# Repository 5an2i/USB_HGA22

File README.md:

# USB_HGA22
HGA22 RF signal receiver with STM32C071 Cortex-M0+ MCU with USB interface

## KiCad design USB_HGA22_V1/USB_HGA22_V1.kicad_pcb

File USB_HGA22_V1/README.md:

# Project Summary - USB_HGA22_V1

## English Description

### Overview
USB_HGA22_V1 is a hardware and software project designed to receive and process signals from the **HGA22** transmitter located in Lakihegy, Hungary. The HGA22 station operates at 135.6 kHz using FSK modulation as part of the EFR Teleswitch system. Unlike standard DCF77 receivers, HGA22 provides much faster time synchronization (every 10 seconds). This project interfaces the receiver with a computer via USB using a modern STM32C071 microcontroller.

### Technical Details
- Microcontroller: **STM32C071** (Arm Cortex-M0+, featuring crystal-less USB support).
- Signal Source: HGA22 (135.6 kHz, FSK modulation, 200 bps).
- Functionality: Decoding the EFR/Teleswitch protocol for precise time acquisition and power management command monitoring.
- Connection: USB 2.0 Full Speed (CDC or HID class) for direct PC integration.

### Key Features
- High-speed synchronization compared to traditional longwave time signals.
- Utilization of the internal 48 MHz RC oscillator (CRS) of the STM32C071 for crystal-less USB communication.
- Low-power design suitable for continuous background operation.

---

## Magyar nyelvű összefoglaló

### Áttekintés
Az USB_HGA22_V1 egy hardveres és szoftveres projekt, amelyet a lakihegyi **HGA22** adó jeleinek vételére és feldolgozására terveztek. A HGA22 állomás 135,6 kHz-es frekvencián, FSK modulációval sugároz az európai EFR Teleswitch rendszer részeként. A DCF77-tel ellentétben a HGA22 sokkal gyakoribb (10 másodpercenkénti) időszinkronizációt tesz lehetővé. A projekt egy modern STM32C071 mikrokontroller segítségével illeszti a vevőegységet a számítógéphez USB-n keresztül.

### Technikai részletek
- Mikrokontroller: **STM32C071** (Arm Cortex-M0+, integrált USB támogatással).
- Jelforrás: HGA22 (135,6 kHz, FSK moduláció, 200 bps adatsebesség).
- Funkció: Az EFR/Teleswitch protokoll dekódolása pontos időnyeréshez vagy vezérlési parancsok (pl. tarifaváltás) monitorozásához.
- Kapcsolat: USB 2.0 Full Speed interfész a közvetlen PC-s kapcsolathoz.

### Főbb jellemzők
- A hagyományos hosszúhullámú időjelekhez képest lényegesen gyorsabb szinkronizáció.
- Az STM32C071 belső 48 MHz-es oszcillátorának (CRS) használata, így nincs szükség külső kvarckristályra az USB kommunikációhoz.
- Alacsony fogyasztású kialakítás, amely ideális folyamatos háttérüzemre.

## Schematic

### Revision 1.0

## Visuals

### Top View

### Bottom View

### Panelized Board

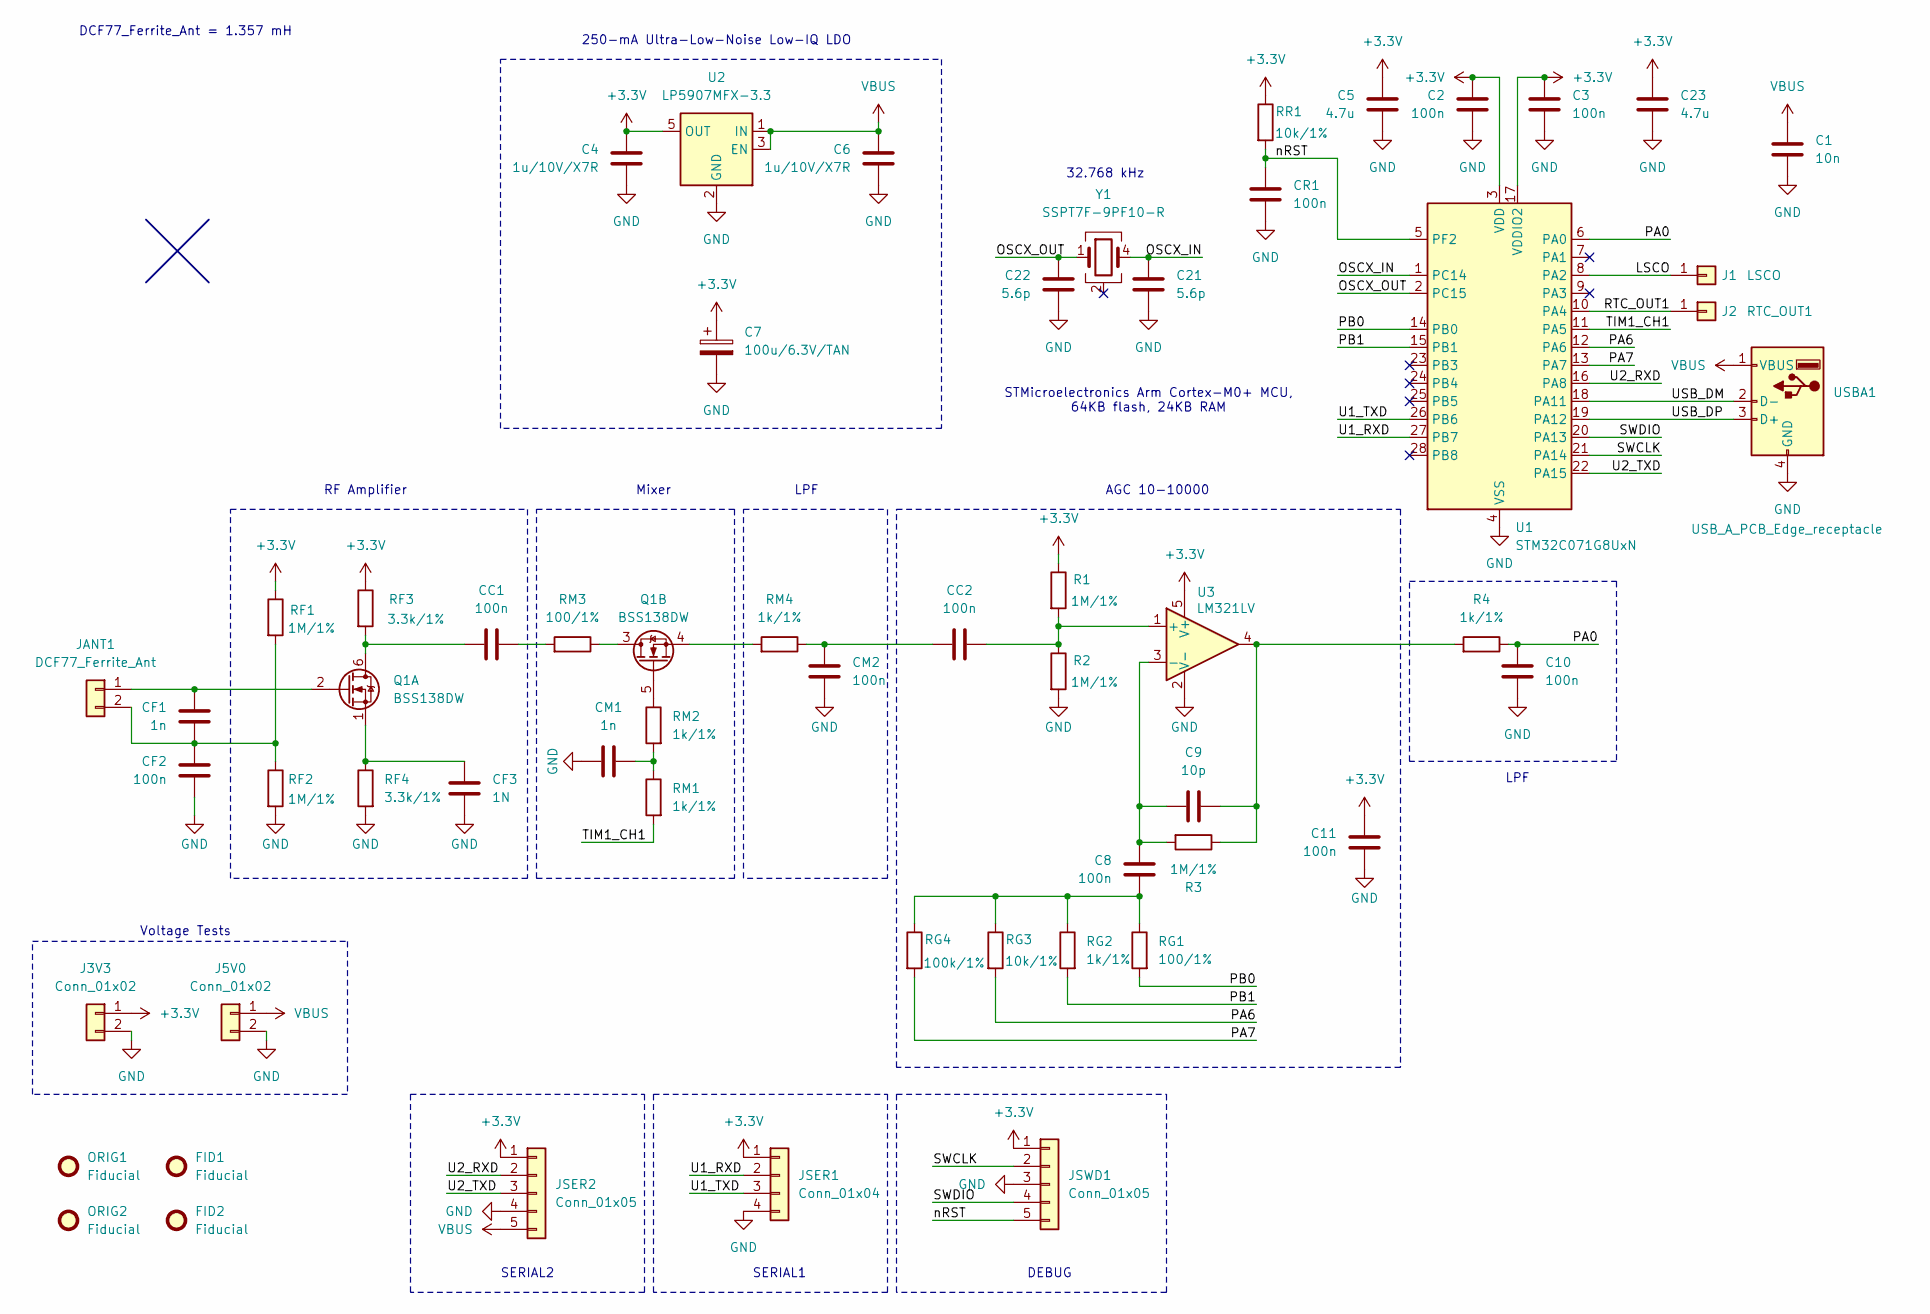
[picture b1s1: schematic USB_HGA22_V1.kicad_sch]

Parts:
C1: 10n; C_0402_1005Metric_Pad0.74x0.62mm_HandSolder
C2, C3, C8, C10, C11: 100n; C_0402_1005Metric_Pad0.74x0.62mm_HandSolder
C4, C6: 1u/10V/X7R; C_0603_1608Metric_Pad1.08x0.95mm_HandSolder
C5, C23: 4.7u; C_0603_1608Metric_Pad1.08x0.95mm_HandSolder
C7: 100u/6.3V/TAN; CP_EIA-3528-21_Kemet-B_HandSolder
C9: 10p; C_0402_1005Metric_Pad0.74x0.62mm_HandSolder
C21, C22: 5.6p; C_0402_1005Metric_Pad0.74x0.62mm_HandSolder
CC1, CC2: 100n; C_0402_1005Metric_Pad0.74x0.62mm_HandSolder
CF1: 1n; C_0805_2012Metric_Pad1.18x1.45mm_HandSolder
CF2: 100n; C_0402_1005Metric_Pad0.74x0.62mm_HandSolder
CF3: 1N; C_0402_1005Metric_Pad0.74x0.62mm_HandSolder
CM1: 1n; C_0402_1005Metric_Pad0.74x0.62mm_HandSolder
CM2: 100n; C_0402_1005Metric_Pad0.74x0.62mm_HandSolder
CR1: 100n; C_0402_1005Metric_Pad0.74x0.62mm_HandSolder
FID1, FID2: Fiducial; Fiducial_1.5mm_Mask3mm
J1: LSCO; SolderWirePad_1x01_SMD_1x2mm
J2: RTC_OUT1; SolderWirePad_1x01_SMD_1x2mm
J3V3, J5V0: Conn_01x02; PinHeader_1x02_P2.54mm_Vertical
JANT1: DCF77_Ferrite_Ant; PinHeader_1x02_P2.54mm_Vertical
JSER1: Conn_01x04; PinHeader_1x04_P2.54mm_Vertical
JSER2: Conn_01x05; PinHeader_1x05_P2.54mm_Vertical
JSWD1: Conn_01x05; PinHeader_1x05_P2.54mm_Vertical
ORIG1, ORIG2: Fiducial; Fiducial_Cross_1.5mm_Mask2mm
Q1: BSS138DW; SOT-363_SC-70-6_Handsoldering
R1, R2, R3: 1M/1%; R_0402_1005Metric_Pad0.72x0.64mm_HandSolder
R4: 1k/1%; R_0402_1005Metric_Pad0.72x0.64mm_HandSolder
RF1, RF2: 1M/1%; R_0402_1005Metric_Pad0.72x0.64mm_HandSolder
RF3, RF4: 3.3k/1%; R_0402_1005Metric_Pad0.72x0.64mm_HandSolder
RG1: 100/1%; R_0402_1005Metric_Pad0.72x0.64mm_HandSolder
RG2: 1k/1%; R_0402_1005Metric_Pad0.72x0.64mm_HandSolder
RG3: 10k/1%; R_0402_1005Metric_Pad0.72x0.64mm_HandSolder
RG4: 100k/1%; R_0402_1005Metric_Pad0.72x0.64mm_HandSolder
RM1, RM2, RM4: 1k/1%; R_0402_1005Metric_Pad0.72x0.64mm_HandSolder
RM3: 100/1%; R_0402_1005Metric_Pad0.72x0.64mm_HandSolder
RR1: 10k/1%; R_0402_1005Metric_Pad0.72x0.64mm_HandSolder
U1: STM32C071G8UxN; QFN-28_4x4mm_P0.5mm
U2: LP5907MFX-3.3; SOT-23-5
U3: LM321LV; SOT-23-5
USBA1: USB_A_PCB_Edge_receptacle
Y1: SSPT7F-9PF10-R; Crystal_SMD_Seiko_SSPT7F-4Pin_6.7x1.5mm_HandSoldering

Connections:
+3.3V: C2.1, C3.1, C4.1, C5.1, C7.1, C11.1, C23.1, J3V3.1, JSER1.1, JSER2.1, JSWD1.1, R1.1, RF1.1, RF3.1, RR1.1, U1.3 (VDD), U1.17 (VDDIO2), U2.5 (OUT), U3.5 (V+)
/LSCO: J1.1 (Pin_1_1), U1.8 (PA2)
/OSCX_IN: C21.1, U1.1 (PC14), Y1.4
/OSCX_OUT: C22.1, U1.2 (PC15), Y1.1
/PA0: C10.1, R4.1, U1.6 (PA0)
/PA6: RG3.2, U1.12 (PA6)
/PA7: RG4.2, U1.13 (PA7)
/PB0: RG1.2, U1.14 (PB0)
/PB1: RG2.2, U1.15 (PB1)
/RTC_OUT1: J2.1 (Pin_1_1), U1.10 (PA4)
/SWCLK: JSWD1.2, U1.21 (PA14)
/SWDIO: JSWD1.4, U1.20 (PA13)
/TIM1_CH1: RM1.2, U1.11 (PA5)
/U1_RXD: JSER1.2, U1.27 (PB7)
/U1_TXD: JSER1.3, U1.26 (PB6)
/U2_RXD: JSER2.2, U1.16 (PA8)
/U2_TXD: JSER2.3, U1.22 (PA15)
/USB_DM: U1.18 (PA11), USBA1.2 (D-)
/USB_DP: U1.19 (PA12), USBA1.3 (D+)
/nRST: CR1.1, JSWD1.5, RR1.2, U1.5 (PF2)
GND: C1.2, C2.2, C3.2, C4.2, C5.2, C6.2, C7.2, C10.2, C11.2, C21.2, C22.2, C23.2, CF2.1, CF3.1, CM1.1, CM2.2, CR1.2, J3V3.2, J5V0.2, JSER1.4, JSER2.4, JSWD1.3, R2.2, RF2.2, RF4.2, U1.4 (VSS), U2.2 (GND), U3.2 (V-), USBA1.4 (GND)
unnamed: C8.1, RG1.1, RG2.1, RG3.1, RG4.1
unnamed: C9.2, R3.1, R4.2, U3.4
unnamed: CC1.2, RM3.2
unnamed: CC2.1, CM2.1, RM4.1
unnamed: CM1.2, RM1.1, RM2.2
unnamed: CF1.2, JANT1.1, Q1.2 (G)
unnamed: CF1.1, CF2.2, JANT1.2, RF1.2, RF2.1
unnamed: CC1.1, Q1.6 (D), RF3.2
unnamed: CF3.2, Q1.1 (S), RF4.1
unnamed: Q1.3 (D), RM3.1
unnamed: Q1.5 (G), RM2.1
unnamed: Q1.4 (S), RM4.2
unnamed: CC2.2, R1.2, R2.1, U3.1 (+)
unnamed: C8.2, C9.1, R3.2, U3.3 (-)
VBUS: C1.1, C6.1, J5V0.1, JSER2.5, U2.1 (IN), U2.3 (EN), USBA1.1 (VBUS)

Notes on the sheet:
LPF
Voltage Tests
RF Amplifier
Mixer
DCF77_Ferrite_Ant = 1.357 mH
DEBUG
SERIAL2
AGC 10-10000
STMicroelectronics Arm Cortex-M0+ MCU, 64KB flash, 24KB RAM
250-mA Ultra-Low-Noise Low-IQ LDO
32.768 kHz
SERIAL1

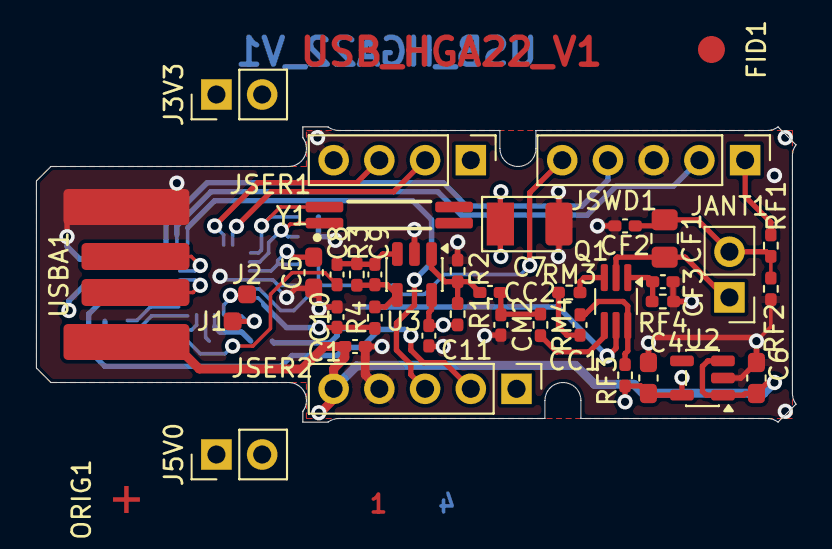
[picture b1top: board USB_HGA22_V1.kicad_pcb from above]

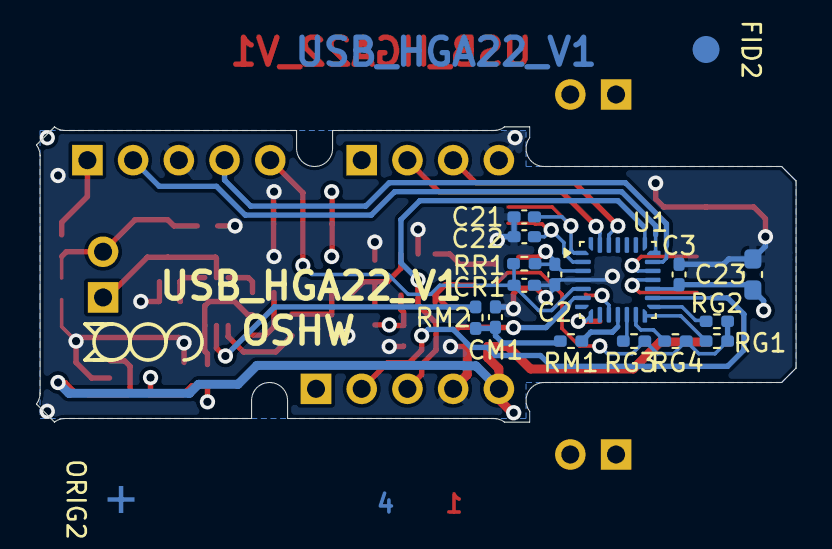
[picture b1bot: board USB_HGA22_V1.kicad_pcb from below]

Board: 4 copper layers, 42.2 x 16.4 mm, 57 parts (17 on the bottom side), 36 nets.

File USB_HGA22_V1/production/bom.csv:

Designator,Footprint,Quantity,Value,LCSC Part #
"C1_6, C1_5, C1_4, C1_3, C1_2, C1",0402,6,10n,
"C10_6, C10_5, C10_4, C10_3, C10_2, C10, C11_6, C11_5, C11_4, C11_3, C11_2, C11, C2_6, C2_5, C2_4, C2_3, C2_2, C2, C3_6, C3_5, C3_4, C3_3, C3_2, C3, C8_6, C8_5, C8_4, C8_3, C8_2, C8, CC1_6, CC1_5, CC1_4, CC1_3, CC1_2, CC1, CC2_6, CC2_5, CC2_4, CC2_3, CC2_2, CC2, CF2_6, CF2_5, CF2_4, CF2_3, CF2_2, CF2, CM2_6, CM2_5, CM2_4, CM2_3, CM2_2, CM2, CR1_6, CR1_5, CR1_4, CR1_3, CR1_2, CR1",0402,60,100n,
"C21_6, C21_5, C21_4, C21_3, C21_2, C21, C22_6, C22_5, C22_4, C22_3, C22_2, C22",0402,12,5.6p,
"C23_6, C23_5, C23_4, C23_3, C23_2, C23, C5_6, C5_5, C5_4, C5_3, C5_2, C5",0603,12,4.7u,
"C4_6, C4_5, C4_4, C4_3, C4_2, C4, C6_6, C6_5, C6_4, C6_3, C6_2, C6",0603,12,1u/10V/X7R,
"C7_6, C7_5, C7_4, C7_3, C7_2, C7",CP_EIA-3528-21_Kemet-B_HandSolder,6,100u/6.3V/TAN,
"C9_6, C9_5, C9_4, C9_3, C9_2, C9",0402,6,10p,
"CF1_6, CF1_5, CF1_4, CF1_3, CF1_2, CF1",0805,6,1n,
"CF3_6, CF3_5, CF3_4, CF3_3, CF3_2, CF3, CM1_6, CM1_5, CM1_4, CM1_3, CM1_2, CM1",0402,12,1N,
"J1_6, J1_5, J1_4, J1_3, J1_2, J1",SolderWirePad_1x01_SMD_1x2mm,6,LSCO,
"J2_6, J2_5, J2_4, J2_3, J2_2, J2",SolderWirePad_1x01_SMD_1x2mm,6,RTC_OUT1,
"J3V3_6, J3V3_5, J3V3_4, J3V3_3, J3V3_2, J3V3, J5V0_6, J5V0_5, J5V0_4, J5V0_3, J5V0_2, J5V0",PinHeader_1x02_P2.54mm_Vertical,12,Conn_01x02,
"JANT1_6, JANT1_5, JANT1_4, JANT1_3, JANT1_2, JANT1",PinHeader_1x02_P2.54mm_Vertical,6,DCF77_Ferrite_Ant,
"JSER1_6, JSER1_5, JSER1_4, JSER1_3, JSER1_2, JSER1",PinHeader_1x04_P2.54mm_Vertical,6,Conn_01x04,
"JSER2_6, JSER2_5, JSER2_4, JSER2_3, JSER2_2, JSER2, JSWD1_6, JSWD1_5, JSWD1_4, JSWD1_3, JSWD1_2, JSWD1",PinHeader_1x05_P2.54mm_Vertical,12,Conn_01x05,
"Q1_6, Q1_5, Q1_4, Q1_3, Q1_2, Q1",SOT-363_SC-70-6_Handsoldering,6,BSS138DW,
"R1_6, R1_5, R1_4, R1_3, R1_2, R1, R2_6, R2_5, R2_4, R2_3, R2_2, R2, R3_6, R3_5, R3_4, R3_3, R3_2, R3, RF1_6, RF1_5, RF1_4, RF1_3, RF1_2, RF1, RF2_6, RF2_5, RF2_4, RF2_3, RF2_2, RF2",0402,30,1M/1%,
"R4_6, R4_5, R4_4, R4_3, R4_2, R4, RG2_6, RG2_5, RG2_4, RG2_3, RG2_2, RG2, RM1_6, RM1_5, RM1_4, RM1_3, RM1_2, RM1, RM2_6, RM2_5, RM2_4, RM2_3, RM2_2, RM2, RM4_6, RM4_5, RM4_4, RM4_3, RM4_2, RM4",0402,30,1k/1%,
"RF3_6, RF3_5, RF3_4, RF3_3, RF3_2, RF3, RF4_6, RF4_5, RF4_4, RF4_3, RF4_2, RF4",0402,12,3.3k/1%,
"RG1_6, RG1_5, RG1_4, RG1_3, RG1_2, RG1, RM3_6, RM3_5, RM3_4, RM3_3, RM3_2, RM3",0402,12,100/1%,
"RG3_6, RG3_5, RG3_4, RG3_3, RG3_2, RG3, RR1_6, RR1_5, RR1_4, RR1_3, RR1_2, RR1",0402,12,10k/1%,
"RG4_6, RG4_5, RG4_4, RG4_3, RG4_2, RG4",0402,6,100k/1%,
"U1_6, U1_5, U1_4, U1_3, U1_2, U1",QFN-28_4x4mm_P0.5mm,6,STM32C071G8UxN,
"U2_6, U2_5, U2_4, U2_3, U2_2, U2",SOT-23-5,6,LP5907MFX-3.3,
"U3_6, U3_5, U3_4, U3_3, U3_2, U3",SOT-23-5,6,LM321LV,
"USBA1_6, USBA1_5, USBA1_4, USBA1_3, USBA1_2, USBA1",USB_A_PCB_Edge_receptacle,6,USB_A_PCB_Edge_receptacle,
"Y1_6, Y1_5, Y1_4, Y1_3, Y1_2, Y1",Crystal_SMD_Seiko_SSPT7F-4Pin_6.7x1.5mm_HandSoldering,6,SSPT7F-9PF10-R,

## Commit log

2026-04-08 Initial project upload.
2026-04-08 Upload README.md
2026-04-09 Documentation uploaded.
2026-04-09 Correcting new section format.
